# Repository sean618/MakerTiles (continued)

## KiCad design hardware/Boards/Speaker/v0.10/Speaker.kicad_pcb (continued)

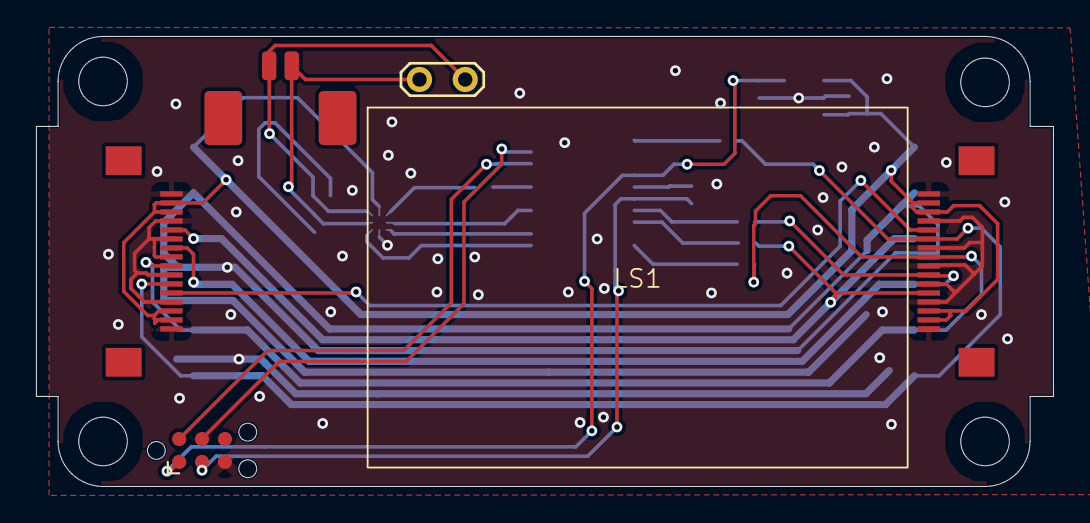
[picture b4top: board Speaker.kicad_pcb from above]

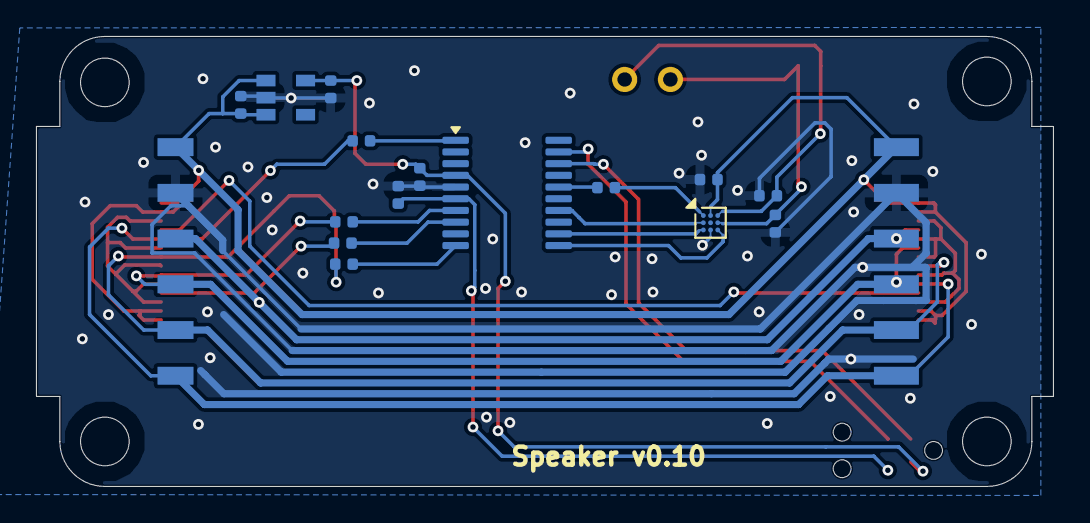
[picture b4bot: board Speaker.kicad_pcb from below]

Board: 2 copper layers, 56.5 x 25.0 mm, 28 parts (17 on the bottom side), 22 nets.
